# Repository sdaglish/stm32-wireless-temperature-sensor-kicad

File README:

# Version Control

## v0.3.0
27 August 2020

* First PCB version after perfboard testing

## v0.2
07 July 2020

* First version of finished schematic and PCB design
* Using CR2032 coin battery - might change this in the near future
* PCB not manufactured and will probably be changed before being shipped for manufacturing
* Tested on perfboard for prototyping

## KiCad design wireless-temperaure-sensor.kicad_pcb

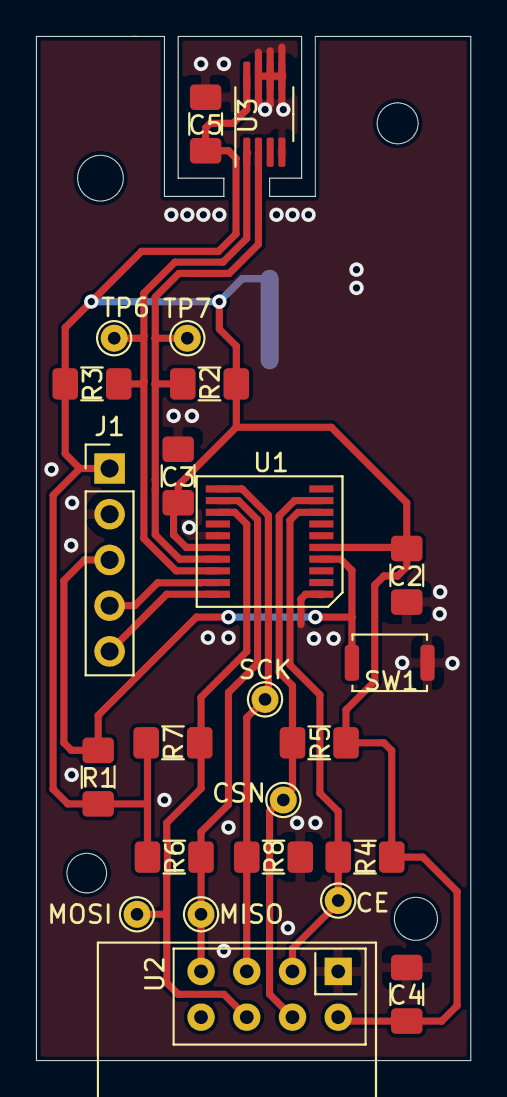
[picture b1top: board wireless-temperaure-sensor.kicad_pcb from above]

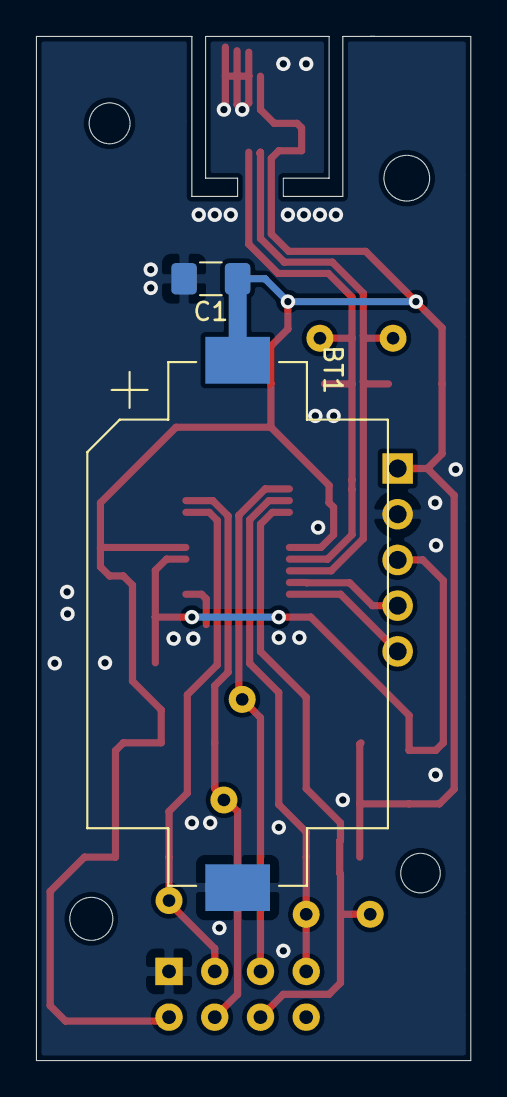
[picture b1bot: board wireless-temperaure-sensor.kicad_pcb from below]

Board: 2 copper layers, 24.1 x 56.9 mm, 26 parts (2 on the bottom side), 12 nets.

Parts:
BT1: Battery_Cell; BatteryHolder_Keystone_1060_1x2032
C1, C2, C3, C4, C5: C; C_1206_3216Metric_Pad1.42x1.75mm_HandSolder
CE: TestPoint_THTPad_D1.5mm_Drill0.7mm
CSN: TestPoint_THTPad_D1.5mm_Drill0.7mm
J1: Programmer; PinHeader_1x05_P2.54mm_Vertical
MISO: TestPoint_THTPad_D1.5mm_Drill0.7mm
MOSI: TestPoint_THTPad_D1.5mm_Drill0.7mm
R1, R2, R3, R4, R5, R6, R7, R8: R; R_1206_3216Metric_Pad1.42x1.75mm_HandSolder
SCK: TestPoint_THTPad_D1.5mm_Drill0.7mm
SW1: SW_Push; SW_Push_SPST_NO_Alps_SKRK
TP6, TP7: TestPoint_THTPad_D1.5mm_Drill0.7mm
U1: stm32l010f4
U2: NRF24L01_Breakout; nRF24L01_Breakout
U3: MCP9808_MSOP; MSOP-8_3x3mm_P0.65mm

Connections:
/MISO: MISO.1, R6.2, U1.12, U2.7
/MOSI: MOSI.1, R7.2, U1.13, U2.6
/NCSN: CSN.1, R5.2, U1.9, U2.4
/NRF_CE: CE.1, R4.2, U1.8, U2.3
/NRST: J1.3, R1.2, SW1.1, U1.4
/SCL: R2.2, TP7.1, U1.17, U3.2
/SDA: R3.2, TP6.1, U1.18, U3.1
/SPI_SCK: R8.1, SCK.1, U1.11, U2.5
/SWCLK: J1.5, U1.20
/SWDIO: J1.4, U1.19
GND: BT1.2, C1.2, C2.2, C3.2, C4.2, C5.2, J1.2, R8.2, SW1.2, U1.1, U1.15, U2.1, U3.4, U3.5, U3.6, U3.7
VDD: BT1.1, C1.1, C2.1, C3.1, C4.1, C5.1, J1.1, R1.1, R2.1, R3.1, R4.1, R5.1, R6.1, R7.1, U1.5, U1.16, U2.2, U3.8

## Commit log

2020-07-24 Project init
2020-07-24 Adding gitignore
2020-07-24 Finalised first draft version of PCB
2020-07-24 Removed ignore files and added revison number
2020-07-24 Added README with version control information
2020-07-24 Added tact switch to schematic
2020-08-15 Finished schematic and almost finished pcb
2020-08-15 Added updated pdf
2020-08-27 Added gerber and drill files#
2020-08-27 Cleaning up
2020-08-27 Creating zip for release manufacturing files
2020-08-27 Updated project version of schematic
2020-08-27 Updated project version on pcb page
2020-08-27 Created pdf of latest version
2020-08-27 Added version information to README
